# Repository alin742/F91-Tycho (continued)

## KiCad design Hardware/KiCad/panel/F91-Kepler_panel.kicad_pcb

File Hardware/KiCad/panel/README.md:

# F91 Tycho JLCPCB panel

`F91-Kepler_panel.kicad_pcb`: **4 main boards (2 × 2) + 4 charging PCBs** in an 83.9 × 71.9 mm frame
(5 mm frame, 3 fiducials, 3 tooling holes, mouse-bite tabs, no V-cut because of the castellated button
contacts). Built with KiKit by `panelize.py`. `fab/` holds everything to upload.

## Order (jlcpcb.com)
1. **PCB:** upload `fab/F91-Kepler_panel_gerbers.zip`.
   - Layers 2, thickness **0.8 mm**, surface finish **ENIG**, **castellated holes: yes**.
   - Panel by customer (the file already is the panel), quantity 5.
   - Via covering: tented (the board file tents every via; vias under the cell must stay covered).
2. **PCB Assembly:** **Standard**, **top side only**, assemble 2 panels (= 8 watches).
   - BOM: `fab/F91-Kepler_panel_BOM.csv`. CPL: `fab/F91-Kepler_panel_CPL.csv`.
   - Bottom side: nothing to assemble (FFC pads, battery pads and antenna only).
3. **Check in JLC's placement preview** that every part sits on its pads with pin 1 right, especially
   U1 (QFN), U2/U3 (DSBGA, X-ray is automatic), Q1–Q3 (DFN1006), J1 (Molex), D1/D2 on the charging PCBs.
   The footprints of all LCSC parts come from LCSC itself, so their rotation should already match.
4. Check stock on the day: CC2640R2FRGZR had 600, BQ25180YBGR 2927, TPS62840YBGR 2074 (2026-11-22).

Extended parts (one-time fee each): CC2640R2FRGZR, BQ25180, TPS62840, MPH160809S2R2MT, PMZB290UNE,
PMEG3002AEL, TPD1E10B06, Molex 505066, BLM18HE152SN1D, 24 MHz crystal, 2 nH and 2.4 nH RF inductors,
1.8 pF, 1.74 kΩ. The 1 pF, 6.8 pF and 10 MΩ are "preferred extended" (no fee); the rest are Basic.

## Expected DRC on the panel
Only the castellated button contacts (`SW1–SW3`) are flagged for copper at the board edge: they are
half-holes on purpose (the clamp arm touches them, as on v1). Everything else is clean, 0 unconnected.

Regenerate: `../../../tools/kikit-venv/bin/python panelize.py && python3 export_fab.py`.

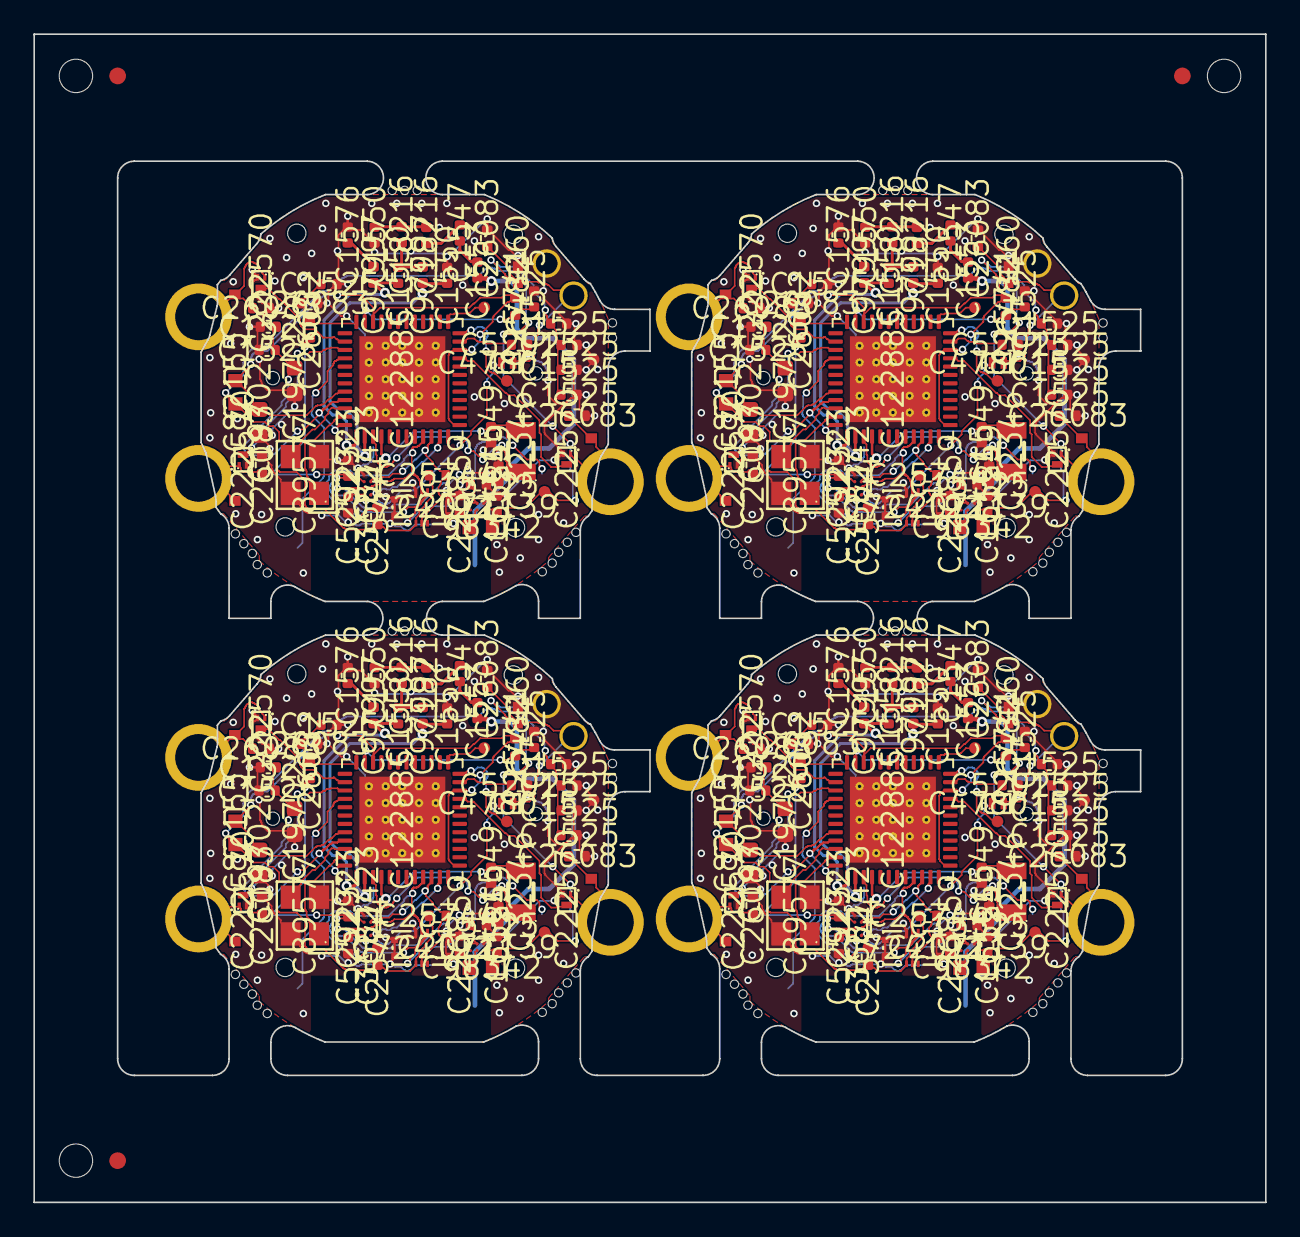
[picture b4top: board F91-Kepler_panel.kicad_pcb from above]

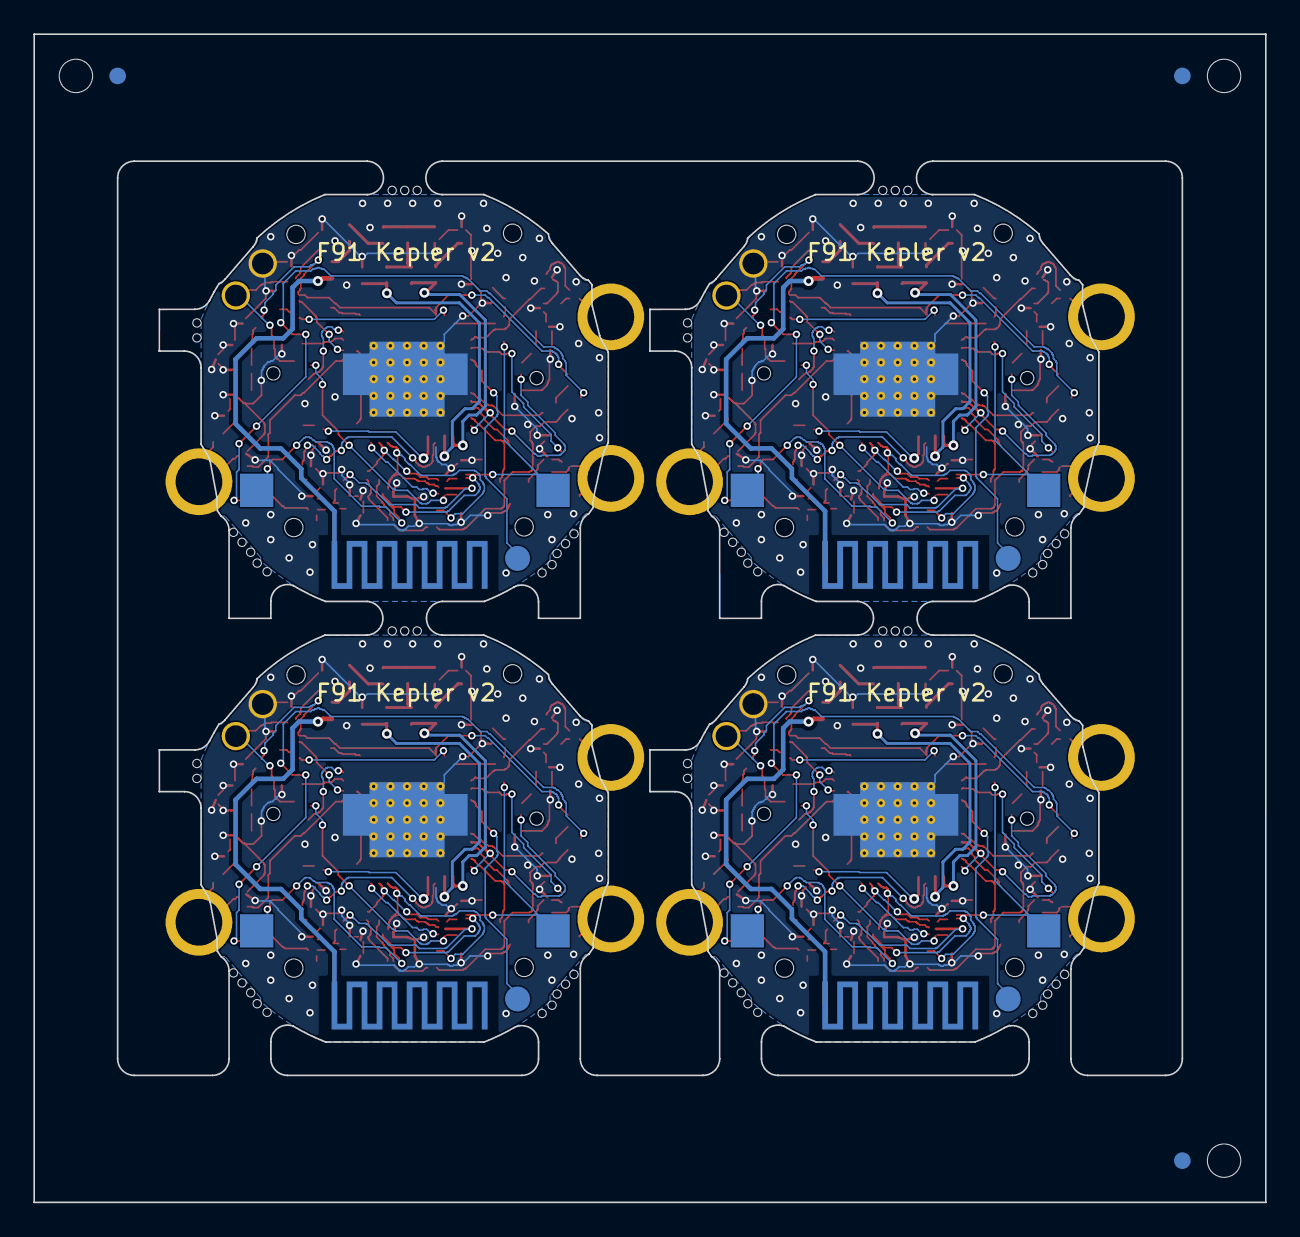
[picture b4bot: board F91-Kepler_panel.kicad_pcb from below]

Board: 2 copper layers, 73.8 x 70.0 mm, 353 parts (3 on the bottom side), 148 nets.

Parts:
AE1_M1, AE1_M2, AE1_M3, AE1_M4: PCB antenna; ANT_TI_MEANDER_B
BT1_M1, BT1_M2, BT1_M3, BT1_M4: LIR2016; BAT_LIR2016_CLAMP
C3_M1, C3_M2, C3_M3, C3_M4, C4_M1, C4_M2, C4_M3, C4_M4, C5_M1, C5_M2, C5_M3, C5_M4, C7_M1, C7_M2, C7_M3, C7_M4, C9_M1, C9_M2, C9_M3, C9_M4, C16_M1, C16_M2, C16_M3, C16_M4, C20_M1, C20_M2, C20_M3, C20_M4, C35_M1, C35_M2, C35_M3, C35_M4: 100nF; C_0402_1005Metric
C6_M1, C6_M2, C6_M3, C6_M4, C8_M1, C8_M2, C8_M3, C8_M4: 10uF; C_0603_1608Metric
C11_M1, C11_M2, C11_M3, C11_M4, C13_M1, C13_M2, C13_M3, C13_M4, C21_M1, C21_M2, C21_M3, C21_M4: 1pF; C_0402_1005Metric
C17_M1, C17_M2, C17_M3, C17_M4, C18_M1, C18_M2, C18_M3, C18_M4: 18pF; C_0402_1005Metric
C19_M1, C19_M2, C19_M3, C19_M4, C30_M1, C30_M2, C30_M3, C30_M4, C33_M1, C33_M2, C33_M3, C33_M4: 1uF; C_0402_1005Metric
C24_M1, C24_M2, C24_M3, C24_M4: 12pF; C_0402_1005Metric
C31_M1, C31_M2, C31_M3, C31_M4: 6.8pF; C_0402_1005Metric
C32_M1, C32_M2, C32_M3, C32_M4, C34_M1, C34_M2, C34_M3, C34_M4: 10uF; C_0402_1005Metric
C51_M1, C51_M2, C51_M3, C51_M4: 1.8pF; C_0402_1005Metric
D1_M1, D1_M2, D1_M3, D1_M4: PMEG3002AEL; SOD-882_L1.0-W0.6-RD
D2_M1, D2_M2, D2_M3, D2_M4: TPD1E10B06; X1SON-2_L1.0-W0.6-P0.65-BI-1
FL1_M1, FL1_M2, FL1_M3, FL1_M4: BLM18HE152SN1D; L0603
J1_M1, J1_M2, J1_M3, J1_M4: 505066-0622; CONN-SMD_5050660622
KiKit_FID_B_1, KiKit_FID_B_2, KiKit_FID_B_3: Fiducial
KiKit_FID_T_1, KiKit_FID_T_2, KiKit_FID_T_3: Fiducial
KiKit_MB_1_3, KiKit_MB_1_4, KiKit_MB_2_3, KiKit_MB_2_4, KiKit_MB_2_5, KiKit_MB_3_3, KiKit_MB_3_4, KiKit_MB_3_5, KiKit_MB_3_6, KiKit_MB_3_7, KiKit_MB_4_3, KiKit_MB_4_4, KiKit_MB_4_5, KiKit_MB_4_6, KiKit_MB_4_7, KiKit_MB_5_3, KiKit_MB_5_4, KiKit_MB_6_3, KiKit_MB_6_4, KiKit_MB_6_5, KiKit_MB_7_3, KiKit_MB_7_4, KiKit_MB_7_5, KiKit_MB_7_6, KiKit_MB_7_7, KiKit_MB_8_3, KiKit_MB_8_4, KiKit_MB_8_5, KiKit_MB_8_6, KiKit_MB_8_7, KiKit_MB_9_3, KiKit_MB_9_4, KiKit_MB_10_3, KiKit_MB_10_4, KiKit_MB_10_5, KiKit_MB_11_3, KiKit_MB_11_4, KiKit_MB_11_5, KiKit_MB_11_6, KiKit_MB_11_7, KiKit_MB_12_3, KiKit_MB_12_4, KiKit_MB_12_5, KiKit_MB_12_6, KiKit_MB_12_7, KiKit_MB_13_3, KiKit_MB_13_4, KiKit_MB_14_3, KiKit_MB_14_4, KiKit_MB_14_5, KiKit_MB_15_3, KiKit_MB_15_4, KiKit_MB_15_5, KiKit_MB_15_6, KiKit_MB_15_7, KiKit_MB_16_3, KiKit_MB_16_4, KiKit_MB_16_5, KiKit_MB_16_6, KiKit_MB_16_7: NPTH
KiKit_TO_1, KiKit_TO_2, KiKit_TO_3: NPTH
L1_M1, L1_M2, L1_M3, L1_M4: 2.2uH; L0603
L11_M1, L11_M2, L11_M3, L11_M4, L21_M1, L21_M2, L21_M3, L21_M4: 2.4nH; L_0402_1005Metric
L12_M1, L12_M2, L12_M3, L12_M4, L13_M1, L13_M2, L13_M3, L13_M4: 2nH; L_0402_1005Metric
MH1_M1, MH1_M2, MH1_M3, MH1_M4, MH2_M1, MH2_M2, MH2_M3, MH2_M4: hole; NPTH_D0.8
MH3_M1, MH3_M2, MH3_M3, MH3_M4, MH4_M1, MH4_M2, MH4_M3, MH4_M4, MH5_M1, MH5_M2, MH5_M3, MH5_M4, MH6_M1, MH6_M2, MH6_M3, MH6_M4: hole; NPTH_D1.1
P1_M1, P1_M2, P1_M3, P1_M4: charge + pin; PIN_PTH_D1.25
P2_M1, P2_M2, P2_M3, P2_M4: charge GND pin; PIN_PTH_D1.25
Q1_M1, Q1_M2, Q1_M3, Q1_M4, Q2_M1, Q2_M2, Q2_M3, Q2_M4, Q3_M1, Q3_M2, Q3_M3, Q3_M4: PMZB290UNE; X1-DFN1006-3_L1.0-W0.6-BR
R1_M1, R1_M2, R1_M3, R1_M4: 100k; R_0402_1005Metric
R2_M1, R2_M2, R2_M3, R2_M4, R3_M1, R3_M2, R3_M3, R3_M4: 10k; R_0402_1005Metric
R11_M1, R11_M2, R11_M3, R11_M4: 1.74k; R_0402_1005Metric
R12_M1, R12_M2, R12_M3, R12_M4: 10M; R_0402_1005Metric
R13_M1, R13_M2, R13_M3, R13_M4, R21_M1, R21_M2, R21_M3, R21_M4, R22_M1, R22_M2, R22_M3, R22_M4, R23_M1, R23_M2, R23_M3, R23_M4, R24_M1, R24_M2, R24_M3, R24_M4: 1M; R_0402_1005Metric
SW1B_M1, SW1B_M2, SW1B_M3, SW1B_M4: button 1 pad; BTN_PAD_0.7x0.6
SW1_M1, SW1_M2, SW1_M3, SW1_M4: button 1 edge contact; BTN_CASTELLATION_D4
SW2B_M1, SW2B_M2, SW2B_M3, SW2B_M4: button 2 pad; BTN_PAD_0.7x0.6
SW2_M1, SW2_M2, SW2_M3, SW2_M4: button 2 edge contact; BTN_CASTELLATION_D4
SW3B_M1, SW3B_M2, SW3B_M3, SW3B_M4: button 3 pad; BTN_PAD_0.7x0.6
SW3_M1, SW3_M2, SW3_M3, SW3_M4: button 3 edge contact; BTN_CASTELLATION_D4
TP1_M1, TP1_M2, TP1_M3, TP1_M4: GND; TP_ROUND_D0.7
TP2_M1, TP2_M2, TP2_M3, TP2_M4: VDD; TP_ROUND_D0.7
TP4_M1, TP4_M2, TP4_M3, TP4_M4: TMSC; TP_ROUND_D0.7
TP5_M1, TP5_M2, TP5_M3, TP5_M4: TCKC; TP_ROUND_D0.7
TP9_M1, TP9_M2, TP9_M3, TP9_M4: BUZZ; PAD_ROUND_D1.5_B
U1_M1, U1_M2, U1_M3, U1_M4: CC2640R2FRGZR; Texas_RGZ0048A_VQFN-48-1EP_7x7mm_P0.5mm_EP5.15x5.15mm_Therm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
U2_M1, U2_M2, U2_M3, U2_M4: BQ25180; DSBGA-8_L1.6-W0.9-R2-C4-P0.40-BL
U3_M1, U3_M2, U3_M3, U3_M4: TPS62840; DSBGA-6_L1.4-W1.0-R2-C3-P0.40-BL
Y1_M1, Y1_M2, Y1_M3, Y1_M4: 32.768kHz; FC-135R_L3.2-W1.5
Y2_M1, Y2_M2, Y2_M3, Y2_M4: 24MHz; CRYSTAL-SMD_4P-L3.2-W2.5-BL

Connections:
M1-ANT: AE1_M1.1, C51_M1.2
M1-BTN1: Q1_M1.3, U1_M1.39
M1-BTN1_PAD: Q1_M1.1, R21_M1.1, SW1B_M1.1, SW1_M1.1
M1-BTN2: Q2_M1.3, U1_M1.38
M1-BTN2_PAD: Q2_M1.1, R22_M1.1, SW2B_M1.1, SW2_M1.1
M1-BTN3: Q3_M1.3, U1_M1.21
M1-BTN3_PAD: Q3_M1.1, R23_M1.1, SW3B_M1.1, SW3_M1.1
M1-BUZZ: TP9_M1.1, U1_M1.40
M1-CHG_IN: D1_M1.2, D2_M1.1, P1_M1.1, R24_M1.1
M1-DCOUPL: C19_M1.1, U1_M1.23
M1-GND: BT1_M1.2, C3_M1.2, C4_M1.2, C5_M1.2, C6_M1.2, C7_M1.2, C8_M1.2, C9_M1.2, C13_M1.2, C16_M1.2, C17_M1.2, C18_M1.2, C19_M1.2, C20_M1.2, C21_M1.2, C30_M1.2, C31_M1.2, C32_M1.2, C33_M1.2, C34_M1.2, C35_M1.2, D2_M1.2, J1_M1.1, J1_M1.7, J1_M1.8, J1_M1.9, J1_M1.10, P2_M1.1, Q1_M1.2, Q2_M1.2, Q3_M1.2, R11_M1.2, R13_M1.2, R21_M1.2, R22_M1.2, R23_M1.2, R24_M1.2, TP1_M1.1, U1_M1.49, U2_M1.D2, U3_M1.A1, Y2_M1.2, Y2_M1.4
M1-PMIC_INT: U1_M1.11, U2_M1.A1
M1-RESET_N: C20_M1.1, R1_M1.2, U1_M1.35
M1-RF_15: C31_M1.1, L11_M1.2
M1-RF_16: C11_M1.2, L12_M1.1, L21_M1.2
M1-RF_17: C13_M1.1, L12_M1.2, L13_M1.1
M1-RF_18: C24_M1.1, L13_M1.2
M1-RF_19: C24_M1.2, C51_M1.1
M1-RF_N: C21_M1.1, L21_M1.1, U1_M1.2
M1-RF_P: C11_M1.1, L11_M1.1, U1_M1.1
M1-SCL: J1_M1.3, R2_M1.2, U1_M1.9, U2_M1.B1
M1-SDA: J1_M1.4, R3_M1.2, U1_M1.10, U2_M1.C1
M1-SW_BUCK: L1_M1.1, U3_M1.B2
M1-SYS: C32_M1.1, U2_M1.B2, U3_M1.B1, U3_M1.C1
M1-TCKC: TP5_M1.1, U1_M1.25
M1-TMSC: TP4_M1.1, U1_M1.24
M1-VBAT: BT1_M1.1, C33_M1.1, J1_M1.5, R12_M1.1, U2_M1.C2
M1-VBAT_SENSE: C35_M1.1, R12_M1.2, R13_M1.1, U1_M1.36
M1-VDD: C34_M1.1, FL1_M1.1, J1_M1.2, L1_M1.2, R2_M1.1, R3_M1.1, TP2_M1.1, U3_M1.A2
M1-VDDR: C8_M1.1, C9_M1.1, C16_M1.1, U1_M1.45, U1_M1.48
M1-VDDS: C3_M1.1, C4_M1.1, C5_M1.1, C6_M1.1, C7_M1.1, FL1_M1.2, R1_M1.1, U1_M1.13, U1_M1.22, U1_M1.34, U1_M1.44
M1-VIN_CHG: C30_M1.1, D1_M1.1, U2_M1.A2
M1-VSET: R11_M1.1, U3_M1.C2
M1-X24M_N: U1_M1.46, Y2_M1.3
M1-X24M_P: U1_M1.47, Y2_M1.1
M1-X32K_1: C17_M1.1, U1_M1.3, Y1_M1.1
M1-X32K_2: C18_M1.1, U1_M1.4, Y1_M1.2
M2-ANT: AE1_M2.1, C51_M2.2
M2-BTN1: Q1_M2.3, U1_M2.39
M2-BTN1_PAD: Q1_M2.1, R21_M2.1, SW1B_M2.1, SW1_M2.1
M2-BTN2: Q2_M2.3, U1_M2.38
M2-BTN2_PAD: Q2_M2.1, R22_M2.1, SW2B_M2.1, SW2_M2.1
M2-BTN3: Q3_M2.3, U1_M2.21
M2-BTN3_PAD: Q3_M2.1, R23_M2.1, SW3B_M2.1, SW3_M2.1
M2-BUZZ: TP9_M2.1, U1_M2.40
M2-CHG_IN: D1_M2.2, D2_M2.1, P1_M2.1, R24_M2.1
M2-DCOUPL: C19_M2.1, U1_M2.23
M2-GND: BT1_M2.2, C3_M2.2, C4_M2.2, C5_M2.2, C6_M2.2, C7_M2.2, C8_M2.2, C9_M2.2, C13_M2.2, C16_M2.2, C17_M2.2, C18_M2.2, C19_M2.2, C20_M2.2, C21_M2.2, C30_M2.2, C31_M2.2, C32_M2.2, C33_M2.2, C34_M2.2, C35_M2.2, D2_M2.2, J1_M2.1, J1_M2.7, J1_M2.8, J1_M2.9, J1_M2.10, P2_M2.1, Q1_M2.2, Q2_M2.2, Q3_M2.2, R11_M2.2, R13_M2.2, R21_M2.2, R22_M2.2, R23_M2.2, R24_M2.2, TP1_M2.1, U1_M2.49, U2_M2.D2, U3_M2.A1, Y2_M2.2, Y2_M2.4
M2-PMIC_INT: U1_M2.11, U2_M2.A1
M2-RESET_N: C20_M2.1, R1_M2.2, U1_M2.35
M2-RF_15: C31_M2.1, L11_M2.2
M2-RF_16: C11_M2.2, L12_M2.1, L21_M2.2
M2-RF_17: C13_M2.1, L12_M2.2, L13_M2.1
M2-RF_18: C24_M2.1, L13_M2.2
M2-RF_19: C24_M2.2, C51_M2.1
M2-RF_N: C21_M2.1, L21_M2.1, U1_M2.2
M2-RF_P: C11_M2.1, L11_M2.1, U1_M2.1
M2-SCL: J1_M2.3, R2_M2.2, U1_M2.9, U2_M2.B1
M2-SDA: J1_M2.4, R3_M2.2, U1_M2.10, U2_M2.C1
M2-SW_BUCK: L1_M2.1, U3_M2.B2
M2-SYS: C32_M2.1, U2_M2.B2, U3_M2.B1, U3_M2.C1
M2-TCKC: TP5_M2.1, U1_M2.25
M2-TMSC: TP4_M2.1, U1_M2.24
M2-VBAT: BT1_M2.1, C33_M2.1, J1_M2.5, R12_M2.1, U2_M2.C2
M2-VBAT_SENSE: C35_M2.1, R12_M2.2, R13_M2.1, U1_M2.36
M2-VDD: C34_M2.1, FL1_M2.1, J1_M2.2, L1_M2.2, R2_M2.1, R3_M2.1, TP2_M2.1, U3_M2.A2
M2-VDDR: C8_M2.1, C9_M2.1, C16_M2.1, U1_M2.45, U1_M2.48
M2-VDDS: C3_M2.1, C4_M2.1, C5_M2.1, C6_M2.1, C7_M2.1, FL1_M2.2, R1_M2.1, U1_M2.13, U1_M2.22, U1_M2.34, U1_M2.44
M2-VIN_CHG: C30_M2.1, D1_M2.1, U2_M2.A2
M2-VSET: R11_M2.1, U3_M2.C2
M2-X24M_N: U1_M2.46, Y2_M2.3
M2-X24M_P: U1_M2.47, Y2_M2.1
M2-X32K_1: C17_M2.1, U1_M2.3, Y1_M2.1
M2-X32K_2: C18_M2.1, U1_M2.4, Y1_M2.2
M3-ANT: AE1_M3.1, C51_M3.2
M3-BTN1: Q1_M3.3, U1_M3.39
M3-BTN1_PAD: Q1_M3.1, R21_M3.1, SW1B_M3.1, SW1_M3.1
M3-BTN2: Q2_M3.3, U1_M3.38
M3-BTN2_PAD: Q2_M3.1, R22_M3.1, SW2B_M3.1, SW2_M3.1
M3-BTN3: Q3_M3.3, U1_M3.21
M3-BTN3_PAD: Q3_M3.1, R23_M3.1, SW3B_M3.1, SW3_M3.1
M3-BUZZ: TP9_M3.1, U1_M3.40
M3-CHG_IN: D1_M3.2, D2_M3.1, P1_M3.1, R24_M3.1
M3-DCOUPL: C19_M3.1, U1_M3.23
M3-GND: BT1_M3.2, C3_M3.2, C4_M3.2, C5_M3.2, C6_M3.2, C7_M3.2, C8_M3.2, C9_M3.2, C13_M3.2, C16_M3.2, C17_M3.2, C18_M3.2, C19_M3.2, C20_M3.2, C21_M3.2, C30_M3.2, C31_M3.2, C32_M3.2, C33_M3.2, C34_M3.2, C35_M3.2, D2_M3.2, J1_M3.1, J1_M3.7, J1_M3.8, J1_M3.9, J1_M3.10, P2_M3.1, Q1_M3.2, Q2_M3.2, Q3_M3.2, R11_M3.2, R13_M3.2, R21_M3.2, R22_M3.2, R23_M3.2, R24_M3.2, TP1_M3.1, U1_M3.49, U2_M3.D2, U3_M3.A1, Y2_M3.2, Y2_M3.4
M3-PMIC_INT: U1_M3.11, U2_M3.A1
M3-RESET_N: C20_M3.1, R1_M3.2, U1_M3.35
M3-RF_15: C31_M3.1, L11_M3.2
M3-RF_16: C11_M3.2, L12_M3.1, L21_M3.2
M3-RF_17: C13_M3.1, L12_M3.2, L13_M3.1
M3-RF_18: C24_M3.1, L13_M3.2
M3-RF_19: C24_M3.2, C51_M3.1
M3-RF_N: C21_M3.1, L21_M3.1, U1_M3.2
M3-RF_P: C11_M3.1, L11_M3.1, U1_M3.1
M3-SCL: J1_M3.3, R2_M3.2, U1_M3.9, U2_M3.B1
M3-SDA: J1_M3.4, R3_M3.2, U1_M3.10, U2_M3.C1
M3-SW_BUCK: L1_M3.1, U3_M3.B2
M3-SYS: C32_M3.1, U2_M3.B2, U3_M3.B1, U3_M3.C1
M3-TCKC: TP5_M3.1, U1_M3.25
M3-TMSC: TP4_M3.1, U1_M3.24
M3-VBAT: BT1_M3.1, C33_M3.1, J1_M3.5, R12_M3.1, U2_M3.C2
M3-VBAT_SENSE: C35_M3.1, R12_M3.2, R13_M3.1, U1_M3.36
M3-VDD: C34_M3.1, FL1_M3.1, J1_M3.2, L1_M3.2, R2_M3.1, R3_M3.1, TP2_M3.1, U3_M3.A2
M3-VDDR: C8_M3.1, C9_M3.1, C16_M3.1, U1_M3.45, U1_M3.48
M3-VDDS: C3_M3.1, C4_M3.1, C5_M3.1, C6_M3.1, C7_M3.1, FL1_M3.2, R1_M3.1, U1_M3.13, U1_M3.22, U1_M3.34, U1_M3.44
M3-VIN_CHG: C30_M3.1, D1_M3.1, U2_M3.A2
M3-VSET: R11_M3.1, U3_M3.C2
M3-X24M_N: U1_M3.46, Y2_M3.3
M3-X24M_P: U1_M3.47, Y2_M3.1
M3-X32K_1: C17_M3.1, U1_M3.3, Y1_M3.1
M3-X32K_2: C18_M3.1, U1_M3.4, Y1_M3.2
M4-ANT: AE1_M4.1, C51_M4.2
M4-BTN1: Q1_M4.3, U1_M4.39
M4-BTN1_PAD: Q1_M4.1, R21_M4.1, SW1B_M4.1, SW1_M4.1
M4-BTN2: Q2_M4.3, U1_M4.38
M4-BTN2_PAD: Q2_M4.1, R22_M4.1, SW2B_M4.1, SW2_M4.1
M4-BTN3: Q3_M4.3, U1_M4.21
M4-BTN3_PAD: Q3_M4.1, R23_M4.1, SW3B_M4.1, SW3_M4.1
M4-BUZZ: TP9_M4.1, U1_M4.40
M4-CHG_IN: D1_M4.2, D2_M4.1, P1_M4.1, R24_M4.1
M4-DCOUPL: C19_M4.1, U1_M4.23
M4-GND: BT1_M4.2, C3_M4.2, C4_M4.2, C5_M4.2, C6_M4.2, C7_M4.2, C8_M4.2, C9_M4.2, C13_M4.2, C16_M4.2, C17_M4.2, C18_M4.2, C19_M4.2, C20_M4.2, C21_M4.2, C30_M4.2, C31_M4.2, C32_M4.2, C33_M4.2, C34_M4.2, C35_M4.2, D2_M4.2, J1_M4.1, J1_M4.7, J1_M4.8, J1_M4.9, J1_M4.10, P2_M4.1, Q1_M4.2, Q2_M4.2, Q3_M4.2, R11_M4.2, R13_M4.2, R21_M4.2, R22_M4.2, R23_M4.2, R24_M4.2, TP1_M4.1, U1_M4.49, U2_M4.D2, U3_M4.A1, Y2_M4.2, Y2_M4.4
M4-PMIC_INT: U1_M4.11, U2_M4.A1
M4-RESET_N: C20_M4.1, R1_M4.2, U1_M4.35
M4-RF_15: C31_M4.1, L11_M4.2
M4-RF_16: C11_M4.2, L12_M4.1, L21_M4.2
M4-RF_17: C13_M4.1, L12_M4.2, L13_M4.1
M4-RF_18: C24_M4.1, L13_M4.2
M4-RF_19: C24_M4.2, C51_M4.1
M4-RF_N: C21_M4.1, L21_M4.1, U1_M4.2
M4-RF_P: C11_M4.1, L11_M4.1, U1_M4.1
M4-SCL: J1_M4.3, R2_M4.2, U1_M4.9, U2_M4.B1
M4-SDA: J1_M4.4, R3_M4.2, U1_M4.10, U2_M4.C1
M4-SW_BUCK: L1_M4.1, U3_M4.B2
M4-SYS: C32_M4.1, U2_M4.B2, U3_M4.B1, U3_M4.C1
M4-TCKC: TP5_M4.1, U1_M4.25
M4-TMSC: TP4_M4.1, U1_M4.24
M4-VBAT: BT1_M4.1, C33_M4.1, J1_M4.5, R12_M4.1, U2_M4.C2
M4-VBAT_SENSE: C35_M4.1, R12_M4.2, R13_M4.1, U1_M4.36
M4-VDD: C34_M4.1, FL1_M4.1, J1_M4.2, L1_M4.2, R2_M4.1, R3_M4.1, TP2_M4.1, U3_M4.A2
M4-VDDR: C8_M4.1, C9_M4.1, C16_M4.1, U1_M4.45, U1_M4.48
M4-VDDS: C3_M4.1, C4_M4.1, C5_M4.1, C6_M4.1, C7_M4.1, FL1_M4.2, R1_M4.1, U1_M4.13, U1_M4.22, U1_M4.34, U1_M4.44
M4-VIN_CHG: C30_M4.1, D1_M4.1, U2_M4.A2
M4-VSET: R11_M4.1, U3_M4.C2
M4-X24M_N: U1_M4.46, Y2_M4.3
M4-X24M_P: U1_M4.47, Y2_M4.1
M4-X32K_1: C17_M4.1, U1_M4.3, Y1_M4.1
M4-X32K_2: C18_M4.1, U1_M4.4, Y1_M4.2

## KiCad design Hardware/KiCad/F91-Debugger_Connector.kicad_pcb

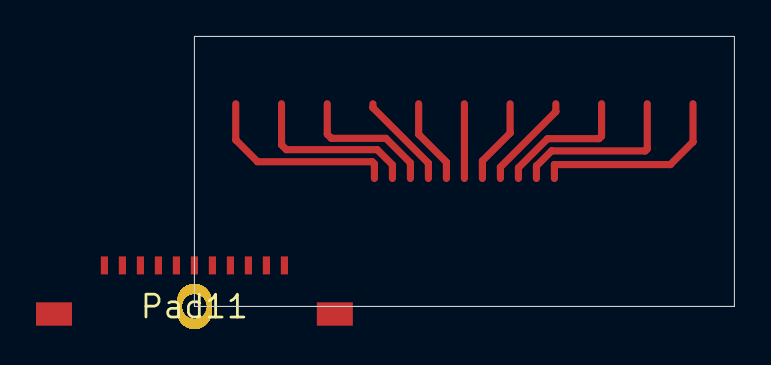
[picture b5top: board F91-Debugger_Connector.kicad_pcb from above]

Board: 2 copper layers, 30.0 x 15.0 mm, 12 parts (0 on the bottom side), 11 nets.

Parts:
200528-1: 11_FPC_MOLEX
Pad1: 51022-0500
Pad2: TB-1x4/2.54/11x7/Sc_H
Pad3, Pad4, Pad5, Pad6, Pad7, Pad8, Pad9, Pad10, Pad11: (no value)

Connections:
Net 0: 200528-1.1, Pad1.1
Net 1: 200528-1.2, Pad2.1
Net 2: 200528-1.3, Pad3.1
Net 3: 200528-1.4, Pad4.1
Net 4: 200528-1.5, Pad5.1
Net 5: 200528-1.6, Pad6.1
Net 6: 200528-1.7, Pad7.1
Net 7: 200528-1.8, Pad8.1
Net 8: 200528-1.9, Pad9.1
Net 9: 200528-1.10, Pad10.1
Net 10: 200528-1.11, Pad11.1

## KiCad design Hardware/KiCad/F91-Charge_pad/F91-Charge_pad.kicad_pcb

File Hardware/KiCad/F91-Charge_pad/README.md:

> **Obsolete since 2026-11-24.** The charging PCB was dropped: the charge contacts are now two brass pins in plated
> holes on the main board (see `TASKS.md`, Rechargeable v2). Kept for reference only; not in the JLC panel.

# F91 Tycho charging PCB

A 13 × 5 mm rigid board (0.8 mm, ENIG) that sits in the round dip of the original steel case back, behind two
Ø1.6 mm holes (one per pogo pin). It is made and assembled in the same JLC panel as the main boards, so it costs no
extra order.

- **Outer face (bottom):** two flush gold pads, Ø1.6 mm, at **2.50 mm pitch** (CHG+ left, GND right as drawn).
  They mate with the bought **Samzo/Einaus 2-pin magnetic pogo male** (`PR5L5015-2P-C-H`: pogos Ø0.9 mm, 8.0 mm magnet spacing).
- **Magnets:** two **Ø3.1 mm holes, 8.0 mm apart**: press in Ø3 × 1 mm N52 magnets with super-glue gel.
  **Check the poles against the cable before gluing:** the bought female half only snaps on one way, so use it to mark the male's N/S ends. Each watch magnet must attract the cable magnet above it.
- **Inner face (top, assembled by JLC):** PMEG3002AEL reverse-polarity Schottky (D1), TPD1E10B06 ESD diode (D2), 1 MΩ pull-down (R1). The outside pad sits at 0 V off the charger.
- **FFC pads (top):** 4 × 1.0 mm pitch (1–2 = VIN to the main board, 3–4 = GND). Solder a ~20 mm piece of 4-way 1.0 mm FFC here and to J2 on the main board's bottom.
- No vias inside the two Ø1.6 mm holes (the wet zone). All four vias are tented and sit under the rubber pad (≥ 0.28 mm from its holes).

## Fitting into the case back (only drill, rubber, tube glue)
1. Practise on a spare F-91W case back.
2. The board goes **inside the round dip** of the case back (Ø23.35, 1.58 deep), flat on the dip floor, under the cell. Peel out the piezo disc (v2 has no buzzer). Drill **two Ø1.6 mm holes, 2.50 mm apart**, one over each gold pad: centred **6.0 mm right of the case-back centre (towards 3 o'clock)**, the two holes stacked 12–6 (1.25 mm above and below that point). The board's long side runs 12–6, FFC edge towards 3 o'clock. Deburr.
   Put Kapton over the board's top: the cell's + can sits ~0.3 mm above it.
3. Cut a 0.5 mm rubber pad (Ø7 mm disc) with **two Ø1.8 mm holes, 2.50 mm apart**, and put it between the PCB and the steel, holes over the pads.
4. Clean and roughen the steel, bed the PCB in **E6000 / MS-polymer**, bead the edges, and cure 24–72 h with the case open.
5. Soak test (30 min, tissue inside) before any electronics go in.

Regenerate: `python3 scripts/gen_charge_pcb.py && python3 scripts/route_charge.py`.

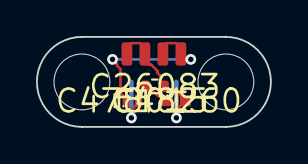
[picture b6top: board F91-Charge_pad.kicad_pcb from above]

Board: 2 copper layers, 13.0 x 5.0 mm, 7 parts (1 on the bottom side), 3 nets.

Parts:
D1: PMEG3002AEL; SOD-882_L1.0-W0.6-RD
D2: TPD1E10B06; X1SON-2_L1.0-W0.6-P0.65-BI-1
J1: pogo contacts 2.5 mm
J2: FFC to main board; FFC4_P1.0_SOLDER_B
MAGL: 3x1 magnet
MAGR: 3x1 magnet
R1: 1M; R_0402_1005Metric

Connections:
CHG_IN: D1.2, D2.1, J1.1, R1.1
GND: D2.2, J1.2, J2.3, J2.4, R1.2
VIN_CHG: D1.1, J2.1, J2.2
